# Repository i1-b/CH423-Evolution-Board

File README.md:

# CH423-Evolution-Board

Evolution board for cost effective I/O expansion operating via 2-wire serial interface.<br> 
It’s great solution for projects based on devices with low pin count. 
Such as ESP8266 /ESP8685.

The evolution board designed for CH423 in SOP28 package: https://www.wch-ic.com/products/CH423.html
<br>Datasheet: https://github.com/i1-b/CH423-Evolution-Board/blob/main/CH423DS1.PDF
<br>Or: https://www.wch-ic.com/downloads/CH432DS1_PDF.html

<h2>Overview</h2>

The CH423 is a universal remote I/O expansion chip with a two-wire serial interface. CH423 provides 8 bidirectional input and output pins and 16 general-purpose output pins to support input level change interrupt. CH423 built-in current drive circuit can statically drive 24 LED tubes or dynamically drive 128 LEDs (equivalent to 16 digital) Tube); CH423 exchanges data with a single-chip microcomputer through a 2-wire serial interface. 

<picture>
   
</picture>

<h2>Features</h2>

    • 8 general-purpose input and output pins GPIO and 16 general-purpose output pin GPOs are remotely extended through a two-wire serial interface. 
    • Built-in current drive stage, continuous drive current is not less than 15mA, OC pin output 1/16 pulse sink current is not less than 120mA. 
    • The static display drive mode supports 24 LEDs or 3 LEDs. 
    • The time-sharing dynamic scanning display drive mode supports 128 LEDs or 16-bit common cathode digital tubes, and supports brightness control. 
    • The bidirectional I/O pin has an interrupt function when the input level changes in the input mode, and the interrupt output is active low. 
    • The 16 general-purpose output pins can be selected for push-pull output or open-drain output. 
    • Supports 3V ~ 5V power supply voltage, supports low-power sleep, can be awakened by input level changes. 
    • High-speed 2-wire serial interface with clock speeds from 0 to 1MHz, compatible with two-wire I2C bus, saving pins.

<h2>Schematic</h2>
https://github.com/i1-b/CH423-Evolution-Board/blob/main/CH423_ev.pdf

<h2>PCB Design</h2>

Repository contains:<br>
<b>/CH423_ev</b>    KiCAD PCB Design Project, including schematic and pcb files.
<br><b>/Prod</b>    GERBER files; drl file also included.

<picture>
   
</picture>

<picture>
   
</picture>

<picture>
   
</picture>

<picture>
   
</picture>

<h2>3D model</h2>
https://github.com/i1-b/CH423-Evolution-Board/blob/main/CH423_ev.step

<h2>Library</h2>

Library: https://github.com/Edragon/WCH-CH42X/tree/main/CH423EVT/EXAM

Arduino library: https://github.com/DFRobot/DFRobot_CH423 <br>
It works with I/O expansion only, dynamic scanning display drive mode unimplemented.

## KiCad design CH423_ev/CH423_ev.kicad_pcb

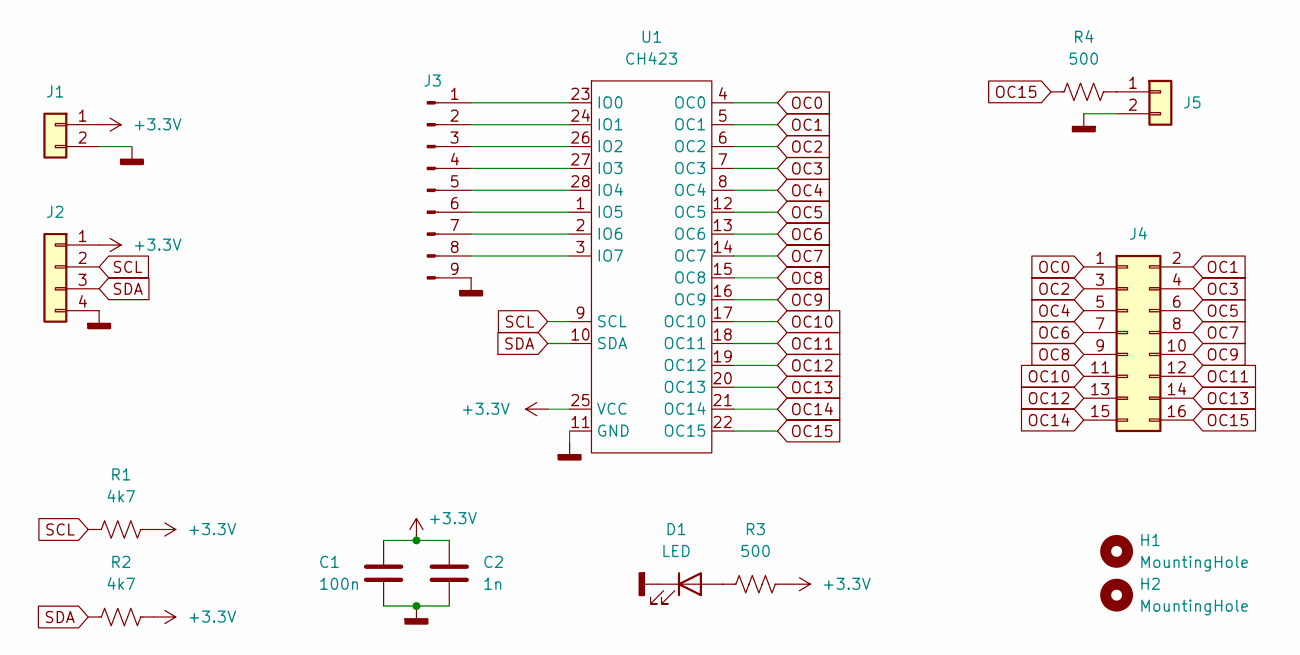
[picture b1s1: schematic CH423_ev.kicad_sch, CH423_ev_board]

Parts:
C1: 100n; C_0402_1005Metric
C2: 1n; C_0402_1005Metric
D1: LED; LED_0603_1608Metric
H1, H2: MountingHole; MountingHole_2.5mm
J1, J5: Conn_01x02; PinHeader_1x02_P2.54mm_Vertical
J2: Conn_01x04; PinHeader_1x04_P2.54mm_Vertical
J3: Conn_01x09_Male; PinHeader_1x09_P2.54mm_Vertical
J4: Conn_02x08_Odd_Even; IDC-Header_2x08_P2.54mm_Vertical
R1, R2: 4k7; R_0402_1005Metric
R3, R4: 500; R_0402_1005Metric
U1: CH423; SOIC-28W_7.5x17.9mm_P1.27mm

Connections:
+3V3: C1.1, C2.1, J1.1, J2.1, R1.2, R2.2, R3.2, U1.25 (VCC)
GNDD: C1.2, C2.2, D1.1 (K), J1.2, J2.4, J3.9, J5.2, U1.11 (GND)
unnamed: D1.2 (A), R3.1
unnamed: J3.1, U1.23 (IO0)
unnamed: J3.2, U1.24 (IO1)
unnamed: J3.3, U1.26 (IO2)
unnamed: J3.4, U1.27 (IO3)
unnamed: J3.5, U1.28 (IO4)
unnamed: J3.6, U1.1 (IO5)
unnamed: J3.7, U1.2 (IO6)
unnamed: J3.8, U1.3 (IO7)
unnamed: J5.1, R4.2
OC0: J4.1, U1.4 (OC0)
OC1: J4.2, U1.5 (OC1)
OC2: J4.3, U1.6 (OC2)
OC3: J4.4, U1.7 (OC3)
OC4: J4.5, U1.8 (OC4)
OC5: J4.6, U1.12 (OC5)
OC6: J4.7, U1.13 (OC6)
OC7: J4.8, U1.14 (OC7)
OC8: J4.9, U1.15 (OC8)
OC9: J4.10, U1.16 (OC9)
OC10: J4.11, U1.17 (OC10)
OC11: J4.12, U1.18 (OC11)
OC12: J4.13, U1.19 (OC12)
OC13: J4.14, U1.20 (OC13)
OC14: J4.15, U1.21 (OC14)
OC15: J4.16, R4.1, U1.22 (OC15)
SCL: J2.2, R1.1, U1.9 (SCL)
SDA: J2.3, R2.1, U1.10 (SDA)

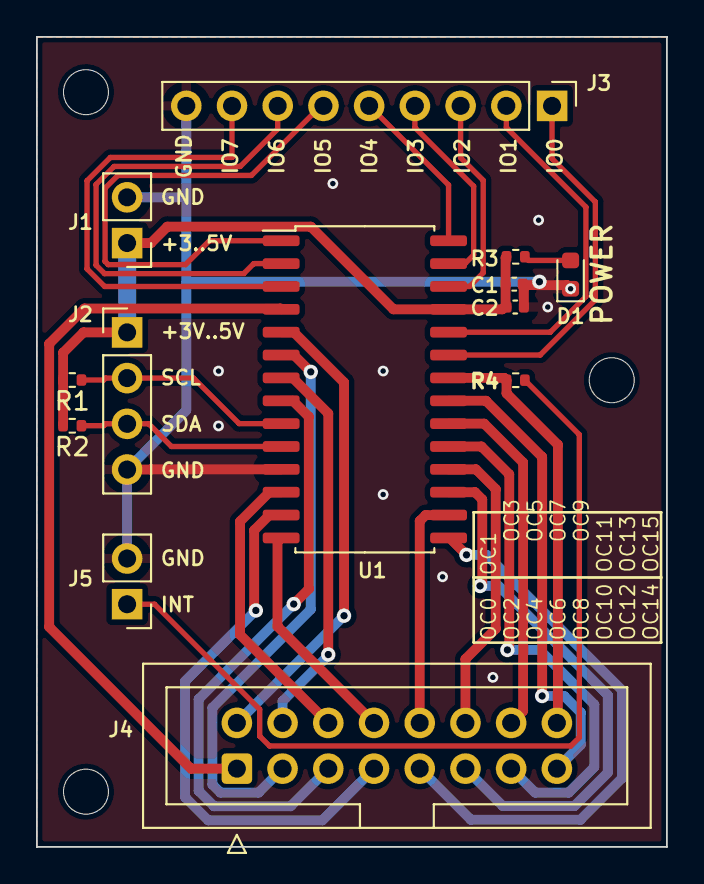
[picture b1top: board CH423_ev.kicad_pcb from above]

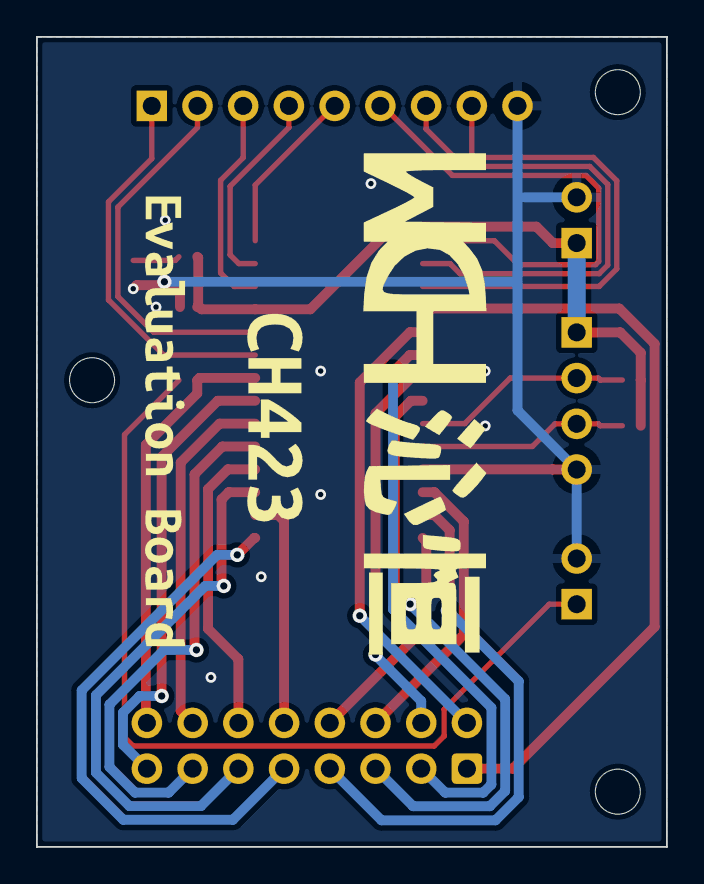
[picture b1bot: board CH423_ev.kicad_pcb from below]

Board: 2 copper layers, 35.0 x 45.0 mm, 18 parts (2 on the bottom side), 30 nets.

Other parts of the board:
H3: MountingHole; MountingHole_2.5mm
kibuzzard-61E6D3CC: G***; kibuzzard-61E6D3CC
kibuzzard-61E6D455: G***; kibuzzard-61E6D455

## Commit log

2024-07-30 Create LICENSE
2024-07-30 Update LICENSE
